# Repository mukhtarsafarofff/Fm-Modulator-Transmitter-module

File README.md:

(ENG) Most of these Short Range FM transmitters plug into the device's headphone jack and then broadcast the signal over an FM broadcast band frequency, so that it can be picked up by any nearby radio.  This allows portable audio devices to make use of the louder or better sound quality of a home audio system or car stereo without requiring a wired connection. Slowly vary the trimmer capacitor, then at a point we can hear some distortion in radio. Then slowly vary in that area, when transmitter and receiver frequency matches you can get the clear output from radio. By tuning the frequency , making of FM transmitter is completed by me. Being low-powered, most transmitters typically have a short range of 100–300 feet (30–100 meters),  depending on the quality of the receiver, obstructions and elevation. Typically they broadcast on any FM frequency from87.5 to 108.0 MHz in most of the world. I take hook up wire of 8-10cm as antenna. By varying the trimmer capacitor ,i can vary the transmission frequency. 

(DEU) Die meisten dieser Kurzstrecken-FM-Sender werden an die Kopfhörerbuchse des Geräts angeschlossen und senden das Signal über eine UKW-Frequenz aus, sodass es von jedem nahegelegenen Radio empfangen werden kann.  Dies ermöglicht es tragbaren Audiogeräten, die lautere oder bessere Klangqualität eines Heim-Audiosystems oder Autoradios zu nutzen, ohne eine kabelgebundene Verbindung zu benötigen. Da sie leistungsschwach sind, haben die meisten Sender normalerweise eine Reichweite von 30–100 Metern (100–300 Fuß), abhängig von der Qualität des Empfängers, Hindernissen und der Höhe. Typischerweise senden sie auf jeder UKW-Frequenz von 87,5 bis 108,0 MHz in den meisten Teilen der Welt. Ich verwende einen Anschlussdraht von 8–10 cm als Antenne. Durch das Verstellen des Trimmkondensators kann ich die Übertragungsfrequenz ändern. Wenn man den Trimmkondensator langsam verstellt, kann man an einem Punkt Verzerrungen im Radio hören. Dann sollte man in diesem Bereich langsam weiterverstellen,und wenn die Frequenzen des Senders und des Empfängers übereinstimmen, erhält man einen klaren Empfang im Radio. Durch das Abstimmen der Frequenz habe ich die Herstellung des FM-Senders abgeschlossen.

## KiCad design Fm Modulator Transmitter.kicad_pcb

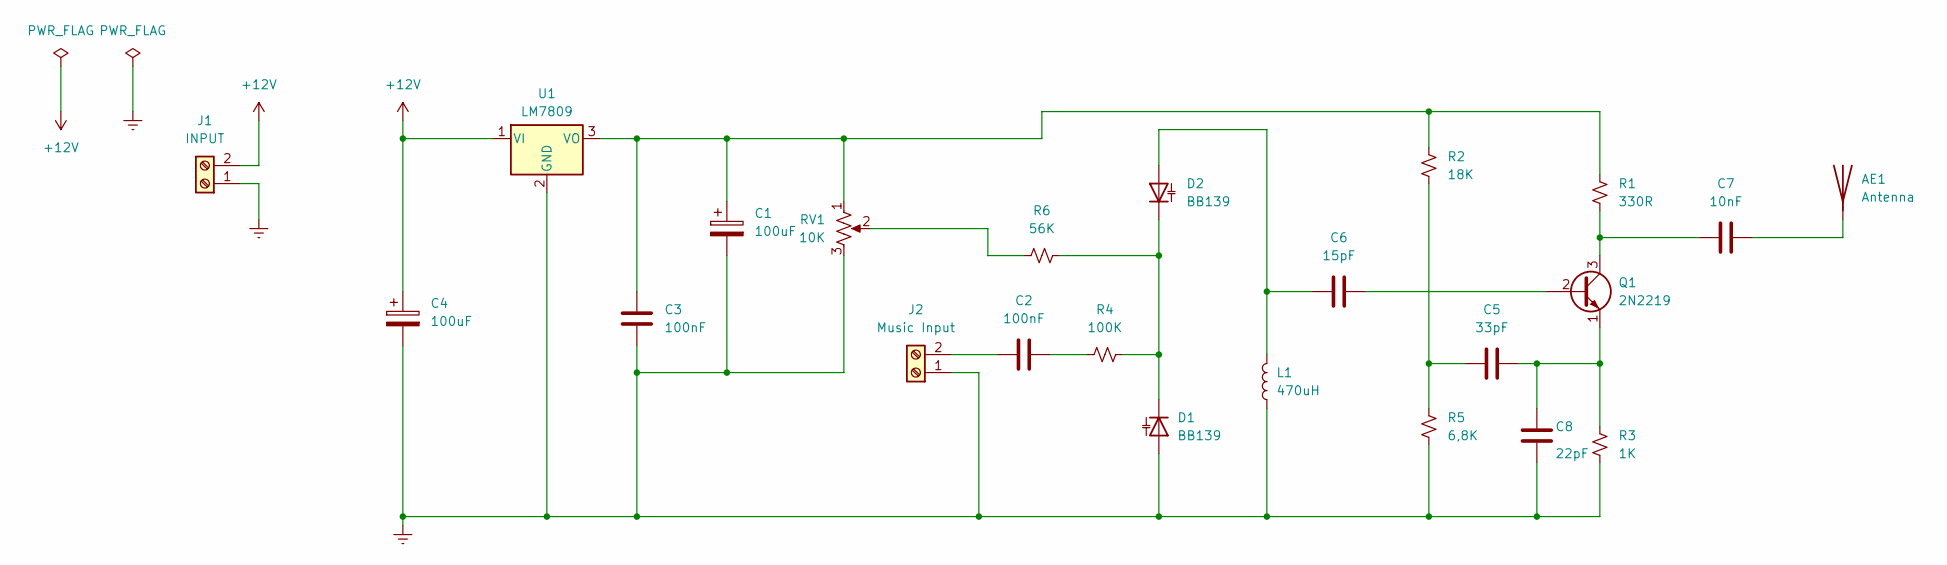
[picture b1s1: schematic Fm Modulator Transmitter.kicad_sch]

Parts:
AE1: Antenna; TerminalBlock_MetzConnect_360271_1x01_Horizontal_ScrewM3.0_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
C1, C4: 100uF; CP_Radial_D10.0mm_P7.50mm
C2, C3: 100nF; C_Disc_D7.5mm_W5.0mm_P7.50mm
C5: 33pF; C_Disc_D7.5mm_W5.0mm_P7.50mm
C6: 15pF; C_Disc_D7.5mm_W5.0mm_P7.50mm
C7: 10nF; C_Disc_D7.5mm_W5.0mm_P7.50mm
C8: 22pF; C_Disc_D7.5mm_W5.0mm_P7.50mm
D1, D2: BB139; D_T-1_P12.70mm_Horizontal
J1: INPUT; TerminalBlock_bornier-2_P5.08mm
J2: Music Input; TerminalBlock_bornier-2_P5.08mm
L1: 470uH; L_Radial_D7.0mm_P3.00mm
Q1: 2N2219; TO-39-3
R1: 330R; R_Axial_DIN0309_L9.0mm_D3.2mm_P15.24mm_Horizontal
R2: 18K; R_Axial_DIN0309_L9.0mm_D3.2mm_P15.24mm_Horizontal
R3: 1K; R_Axial_DIN0309_L9.0mm_D3.2mm_P15.24mm_Horizontal
R4: 100K; R_Axial_DIN0309_L9.0mm_D3.2mm_P15.24mm_Horizontal
R5: 6,8K; R_Axial_DIN0309_L9.0mm_D3.2mm_P15.24mm_Horizontal
R6: 56K; R_Axial_DIN0309_L9.0mm_D3.2mm_P15.24mm_Horizontal
RV1: 10K; Potentiometer_Vishay_148-149_Single_Horizontal
U1: LM7809; TO-220-3_Vertical

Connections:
+12V: C4.1, J1.2, U1.1 (VI)
Earth: C1.2, C3.1, C4.2, C8.1, D1.2 (A), J1.1, J2.1, L1.1, R3.2, R5.2, RV1.3, U1.2 (GND)
unnamed: AE1.1 (A), C7.2
unnamed: C2.2, R4.1
unnamed: C5.1, R2.2, R5.1
unnamed: D1.1 (K), D2.1 (K), R4.2, R6.2
unnamed: C6.1, D2.2 (A), L1.2
unnamed: C2.1, J2.2
unnamed: C6.2, Q1.2 (B)
unnamed: C7.1, Q1.3 (C), R1.2
unnamed: C5.2, C8.2, Q1.1 (E), R3.1
unnamed: R6.1, RV1.2
unnamed: C1.1, C3.2, R1.1, R2.1, RV1.1, U1.3 (VO)

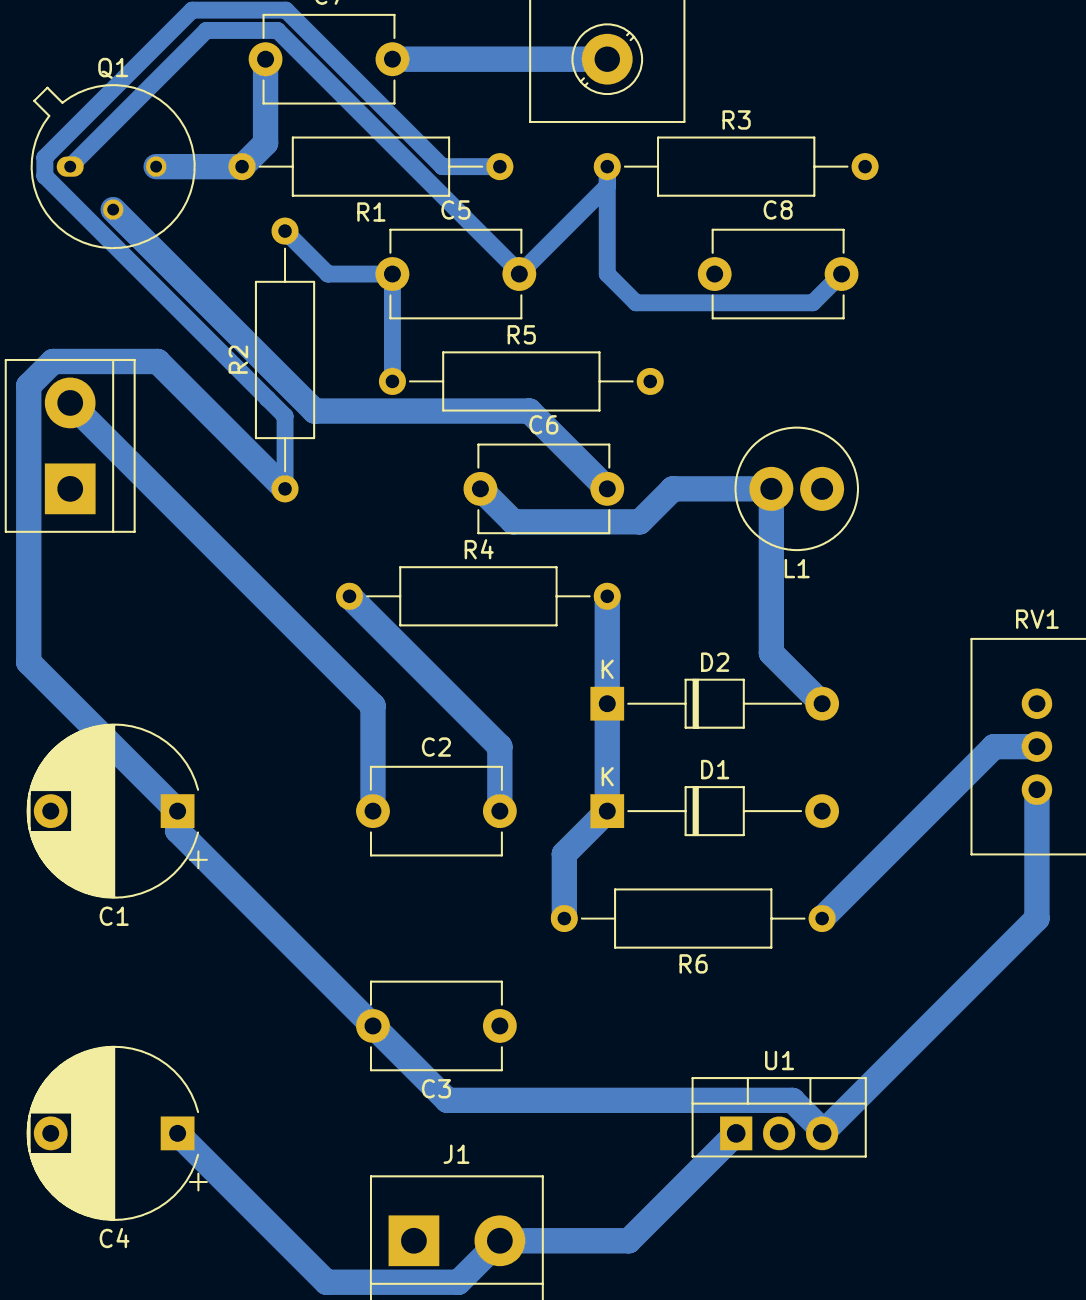
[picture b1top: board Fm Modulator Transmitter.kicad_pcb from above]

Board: 2 copper layers, 23 parts (0 on the bottom side), 13 nets.

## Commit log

2024-03-20 Fm Transmitter is accomplished
2024-03-25 Fm Modulator Transmitter is renewed
